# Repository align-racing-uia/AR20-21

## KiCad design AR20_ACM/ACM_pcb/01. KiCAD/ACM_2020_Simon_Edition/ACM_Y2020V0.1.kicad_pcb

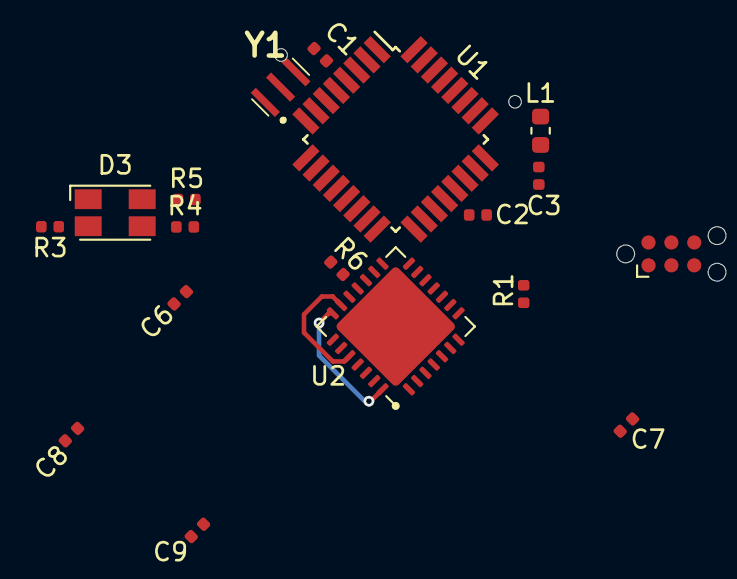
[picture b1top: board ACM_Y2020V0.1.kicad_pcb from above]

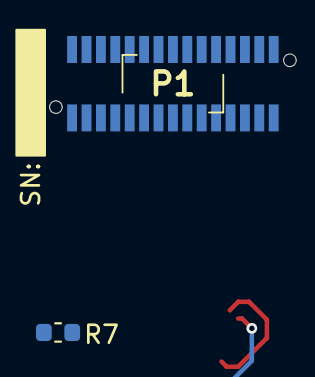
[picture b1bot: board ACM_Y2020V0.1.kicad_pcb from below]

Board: 2 copper layers, 21 parts (2 on the bottom side), 36 nets.

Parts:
C1, C2, C3, C6, C7, C8, C9: 0.1uF; C_0402_1005Metric
D3: ASMB-MTB0-0A3A2; LED_Avago_PLCC4_3.2x2.8mm_CW
H1: M2 Mouting hole; MountingHole_2.2mm_M2
J1: TC2030-MCP-NL; Tag-Connect_TC2030-IDC-NL_2x03_P1.27mm_Vertical
L1: 10uH; L_0603_1608Metric
P1: Conn_02x15_Odd_Even; ILWX10SBVFBE
R1, R6: 10K Ohm; R_0402_1005Metric
R3: 290 ohm; R_0402_1005Metric
R4: 200ohm; R_0402_1005Metric
R5: 190 Ohm; R_0402_1005Metric
R7: 120 Ohm; R_0603_1608Metric
U1: ATmega328P-AU; TQFP-32_7x7mm_P0.8mm
U2: MCP25625-x-SS; QFN-28-1EP_6x6mm_P0.65mm_EP4.8x4.8mm
Y1: 16.0Mhz; CSTNE16M0V530000R0

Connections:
+5V: C1.1, C6.1, D3.1, J1.2, L1.1, P1.27, R1.1, R6.2, U1.4, U1.6, U1.18
/BLUE_LED: P1.19, R5.2, U1.14
/CAN_CS: U1.11, U2.17
/CAN_INT: U1.32, U2.13
/CLK_MCP: U1.12, U2.9
/GREEN_LED: P1.25, R4.2, U1.9
/MISO: J1.1, P1.15, U1.16, U2.16
/MOSI: J1.4, P1.17, U1.15, U2.15
/RED_LED: P1.21, R3.2, U1.13
/Reset: J1.5, P1.10, R1.2
/SCK: J1.3, P1.13, U1.17, U2.14
/U-Pin1: P1.1, R7.2, U2.3
/U-Pin2: P1.2, U1.25
/U-Pin3: P1.3, R7.1, U2.4
/U-Pin4: P1.4, U1.26
/U-Pin6: P1.6, U1.27
/U-Pin7: P1.7, U1.23
/U-Pin8: P1.8, U1.28
/U-Pin12: P1.12, U1.30
/U-Pin14: P1.14, U1.31
/U-Pin20: P1.20, U1.1
/U-Pin22: P1.22, U1.2
/U-Pin23: P1.23, U1.10
GND: C1.2, C2.2, C3.1, C6.2, C7.2, C8.2, C9.1, J1.6, P1.16, P1.18, U1.3, U1.5, U1.21, U2.5, U2.10, U2.26, Y1.2
unnamed: C2.1, U1.20
unnamed: C3.2, L1.2
unnamed: C7.1, C8.1, U2.1, U2.19
unnamed: C9.2, U2.27
unnamed: D3.2, R5.1
unnamed: D3.3, R4.1
unnamed: D3.4, R3.1
unnamed: R6.1, U2.18
unnamed: U1.7, Y1.3
unnamed: U1.8, Y1.1
unnamed: U2.20, U2.24
unnamed: U2.21, U2.28

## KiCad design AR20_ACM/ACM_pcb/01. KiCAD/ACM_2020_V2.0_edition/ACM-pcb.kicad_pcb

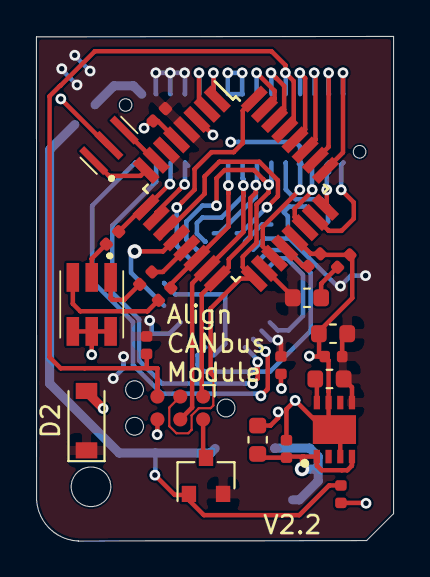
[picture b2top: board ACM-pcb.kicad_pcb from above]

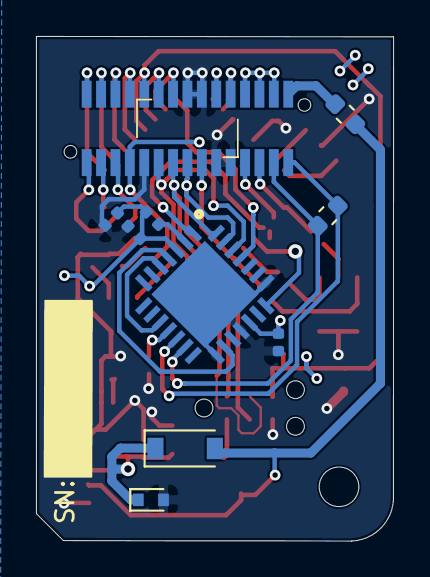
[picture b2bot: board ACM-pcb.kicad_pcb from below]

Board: 2 copper layers, 19.8 x 28.0 mm, 33 parts (11 on the bottom side), 42 nets.

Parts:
C1, C2, C3, C4, C5, C6, C7, C8, C9: 0.1uF; C_0402_1005Metric
C10, C11: 10uF; C_0603_1608Metric
D1: 15V; D_SOD-523
D2: D_Zener_KDZVTR5.6B; D_Zener_KDZV5.6B_SOD-123
D4: D_Schottky_MBR0520LT1G; D_schotky_MBR0520LT1G
F1: 250mA; Fuse_0603_1608Metric
H1: M2 Mouting hole; MountingHole_2.2mm_M2
IC1: MCP25625T-E_ML; QFN65P600X600X100-29N-D
J1: TC2030-MCP-NL; Tag-Connect_TC2030-IDC-NL_2x03_P1.27mm_Vertical
L1: 10uH; L_0603_1608Metric
L2: 2.2 µH; L_0603_1608Metric
LED1: ASMB-TTF0-0A20B; ASMBTTF00A20B
P1: Conn_02x15_Odd_Even; ILWX10SBVFBE
Q1: Q_PMOS_DMP3099L-13; Pmos_DMP3099L-13
R1, R2, R6: 10K Ohm; R_0402_1005Metric
R3: 290 ohm; R_0402_1005Metric
R4: 200ohm; R_0402_1005Metric
R5: 190 Ohm; R_0402_1005Metric
R7: 120 Ohm; R_0603_1608Metric
U1: ATmega328P-AU; TQFP-32_7x7mm_P0.8mm
U3: NCV890430MW50TXG; SON65P300X300X100-9N
Y1: 16.0Mhz; CSTNE16M0V530000R0

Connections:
12V_fused: D4.2, F1.1, Q1.1, R2.2
+5V: C1.1, C5.1, C6.1, C7.1, C8.1, C9.2, C11.1, D2.1, IC1.3, IC1.11, IC1.19, L1.1, L2.2, P1.24, P1.26, P1.28, Q1.2, R1.1, R6.2, U1.4, U1.6, U1.18, U3.5
+12V: F1.2, P1.30
+12V_Safe: C4.1, C10.1, D1.1, D4.1, U3.1, U3.4
/BLUE_LED: P1.17, R5.2, U1.14
/CAN_CS: IC1.1, U1.11
/CAN_INT: IC1.25, U1.32
/CLK_MCP: IC1.21, U1.12
/GREEN_LED: P1.25, R4.2, U1.9
/MISO: IC1.28, J1.1, P1.13, U1.16
/MOSI: IC1.27, J1.4, P1.15, U1.15
/RED_LED: R3.2, U1.13
/Reset: J1.5, P1.10, R1.2, U1.29
/SCK: IC1.26, J1.3, P1.11, U1.17
/U-Pin1: P1.1, U1.23
/U-Pin2: P1.2, U1.25
/U-Pin3: P1.3, U1.24
/U-Pin4: P1.4, U1.26
/U-Pin5: P1.5, U1.22
/U-Pin6: P1.6, U1.27
/U-Pin7: P1.7, U1.19
/U-Pin8: P1.8, U1.28
/U-Pin12: P1.12, U1.30
/U-Pin14: P1.14, U1.31
/U-Pin20: P1.20, U1.1
/U-Pin22: P1.22, U1.2
/U-Pin23: P1.23, U1.10
/U-Pin27: IC1.13, P1.27, R7.1
/U-Pin29: IC1.12, P1.29, R7.2
GND: C1.2, C2.2, C3.1, C4.2, C5.2, C6.2, C7.2, C8.2, C9.1, C10.2, C11.2, D1.2, D2.2, IC1.15, IC1.18, IC1.22, IC1.29, J1.6, LED1.2, LED1.4, LED1.6, P1.9, P1.16, P1.18, P1.19, P1.21, R2.1, U1.3, U1.5, U1.21, U3.3, U3.7, U3.9, Y1.2
unnamed: C2.1, U1.20
unnamed: C3.2, L1.2
unnamed: IC1.2, R6.1
unnamed: IC1.5, IC1.10
unnamed: IC1.4, IC1.16
unnamed: J1.2, Q1.3
unnamed: L2.1, U3.8
unnamed: LED1.1, R3.1
unnamed: LED1.3, R4.1
unnamed: LED1.5, R5.1
unnamed: U1.7, Y1.3
unnamed: U1.8, Y1.1

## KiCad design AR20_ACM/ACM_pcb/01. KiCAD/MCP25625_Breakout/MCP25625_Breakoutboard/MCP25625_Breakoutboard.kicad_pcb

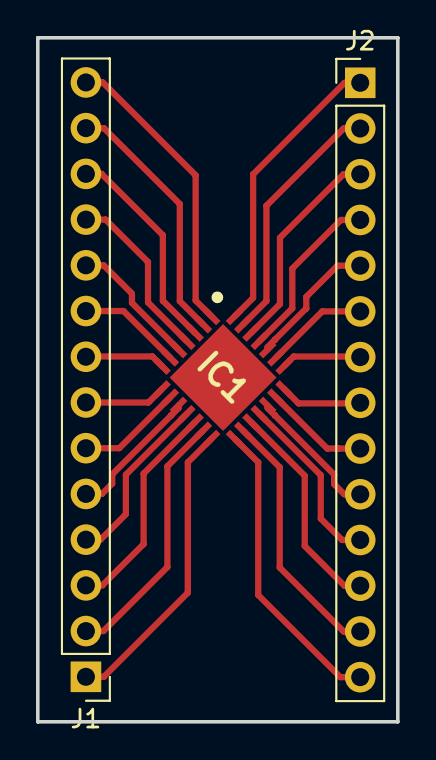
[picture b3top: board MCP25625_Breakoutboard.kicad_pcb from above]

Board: 2 copper layers, 20.0 x 38.0 mm, 3 parts (0 on the bottom side), 28 nets.

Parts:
IC1: MCP25625T-E_ML; QFN65P600X600X100-29N-D
J1, J2: Conn_01x14; PinHeader_1x14_P2.54mm_Vertical

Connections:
/Pin1: IC1.1, J1.14
/Pin2: IC1.2, J1.13
/Pin3: IC1.3, J1.12
/Pin4: IC1.4, J1.11
/Pin5: IC1.5, J1.10
/Pin6: IC1.6, J1.9
/Pin7: IC1.7, J1.8
/Pin8: IC1.8, J1.7
/Pin9: IC1.9, J1.6
/Pin10: IC1.10, J1.5
/Pin11: IC1.11, J1.4
/Pin12: IC1.12, J1.3
/Pin13: IC1.13, J1.2
/Pin14: IC1.14, J1.1
/Pin15: IC1.15, J2.14
/Pin16: IC1.16, J2.13
/Pin17: IC1.17, J2.12
/Pin18: IC1.18, J2.11
/Pin19: IC1.19, J2.10
/Pin20: IC1.20, J2.9
/Pin21: IC1.21, J2.8
/Pin22: IC1.22, J2.7
/Pin23: IC1.23, J2.6
/Pin24: IC1.24, J2.5
/Pin25: IC1.25, J2.4
/Pin26: IC1.26, J2.3
/Pin27: IC1.27, J2.2
/Pin28: IC1.28, J2.1

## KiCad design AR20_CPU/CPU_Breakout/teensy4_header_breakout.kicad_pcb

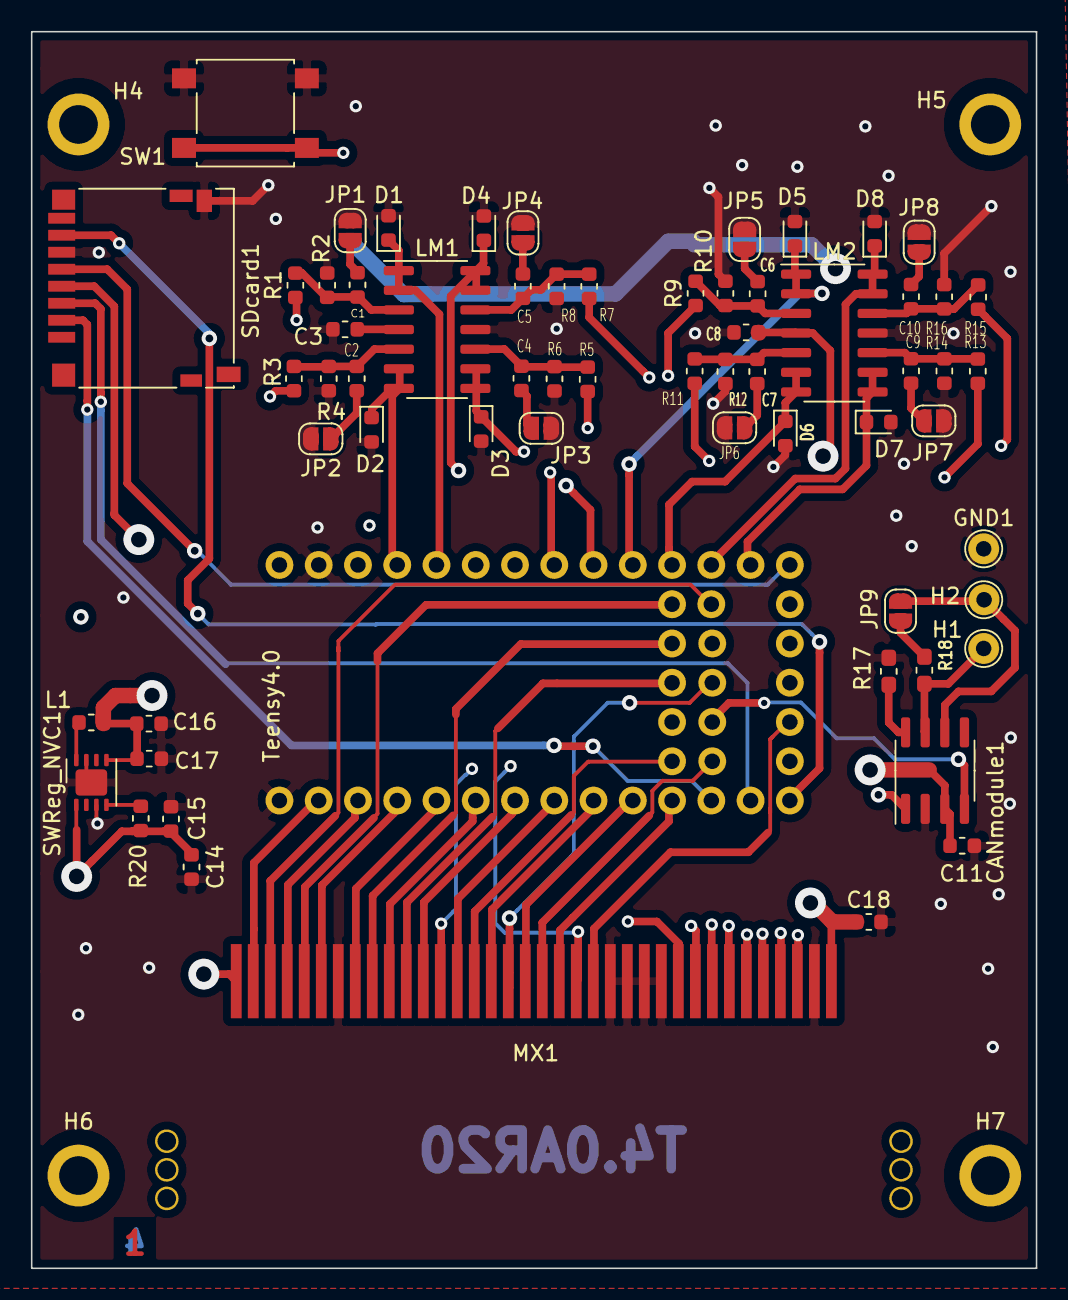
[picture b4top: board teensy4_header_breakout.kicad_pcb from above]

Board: 4 copper layers, 65.0 x 80.0 mm, 69 parts (0 on the bottom side), 69 nets.

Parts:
BT1: 3V cell coin; BatteryHolder_Keystone_3034_1x20mm
C1, C2, C4, C5, C6, C7, C9, C10: 1.5n; C_0603_1608Metric
C3, C8: C; C_0603_1608Metric
C11: .1u; C_0603_1608Metric
C14, C17, C18: 10u; C_0603_1608Metric
C15, C16: 0.1u; C_0603_1608Metric
CANmodule1: MCP2551-I-SN; SOIC-8_3.9x4.9mm_P1.27mm
D1, D2, D3, D4, D5, D6, D7, D8: 3V; D_0603_1608Metric
GND1: GND; TestPoint_THTPad_D2.0mm_Drill1.0mm
H1: CANH_out; TestPoint_THTPad_D2.0mm_Drill1.0mm
H2: CANL_out; TestPoint_THTPad_D2.0mm_Drill1.0mm
H4, H5, H6, H7: MountingHole; MountingHole_2.5mm_Pad
JP1, JP2, JP3, JP4, JP5, JP6, JP7, JP8: SJ_Open; SolderJumper-2_P1.3mm_Open_RoundedPad1.0x1.5mm
JP9: SolderJumper_2_Open; SolderJumper-2_P1.3mm_Open_RoundedPad1.0x1.5mm
L1: 2.2u; L_0603_1608Metric
LM1, LM2: LM324DRG3; SOIC-14_3.9x8.7mm_P1.27mm
MX1: MX34_36_pins; Connector_MX34_36pins
R1, R3, R5, R7, R9, R11, R13, R15, R20: 10k; R_0603_1608Metric
R2, R4, R6, R8, R10, R12, R14, R16: 20k; R_0603_1608Metric
R17: 60; R_0603_1608Metric_Pad1.05x0.95mm_HandSolder
R18: 120; R_0603_1608Metric_Pad1.05x0.95mm_HandSolder
SDcard1: Micro_SD_Card; microSD_HC_Hirose_DM3D-SF
SW1: SW_Push_Dual; SW_SPST_B3S-1000
SWReg_NVC1: NCV890430MW50TXG; DFN-8-1EP_3x3mm_P0.65mm_EP1.7x2.05mm
Teensy4.0: Teensy_pins; Teensy_40_footprint

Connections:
0_RX1: MX1.1, Teensy4.0.3
1_TX1: MX1.3, Teensy4.0.5
2_OUT2: MX1.5, Teensy4.0.7
3.3V: MX1.21, SDcard1.4, Teensy4.0.6, Teensy4.0.30
3_LRCLK2: MX1.7, Teensy4.0.9
4_BCLK2: MX1.9, Teensy4.0.11
5_IN2: MX1.11, Teensy4.0.13
6_OUT1D: MX1.13, Teensy4.0.15
7_RX2_OUT1A: MX1.15, Teensy4.0.17
8_TX2_IN1: MX1.17, Teensy4.0.19
9_OUT1C: MX1.19, Teensy4.0.21
10_CS: SDcard1.2, Teensy4.0.23
11_MOSI: SDcard1.3, Teensy4.0.25
12V_IN: C14.1, C15.1, C18.1, MX1.52, R20.1, SWReg_NVC1.1
12_MISO: SDcard1.7, Teensy4.0.27
13(LED): SDcard1.5, Teensy4.0.28
20_TX5: MX1.39, Teensy4.0.14
21_RX5: MX1.37, Teensy4.0.12
24_TX6_A10: MX1.22, Teensy4.0.38
25_RX6_A11: MX1.24, Teensy4.0.43
27_A13: MX1.38, Teensy4.0.42
28_RX7: MX1.36, Teensy4.0.36
29_TX7: MX1.42, Teensy4.0.41
30_CRX3: CANmodule1.4, Teensy4.0.35
31_CTX3: CANmodule1.1, Teensy4.0.40
32_OUT1B: MX1.40, Teensy4.0.34
33_MCLK2: MX1.41, Teensy4.0.39
Ground: BT1.2, C3.1, C8.1, C11.2, C14.2, C15.2, C16.2, C17.2, C18.2, CANmodule1.2, D1.2, D2.2, D3.2, D4.2, D5.2, D6.2, D7.2, D8.2, GND1.1, JP1.2, JP2.2, JP3.2, JP4.2, JP5.2, JP6.2, JP7.2, JP8.2, LM1.11, LM2.11, MX1.26, MX1.30, MX1.34, MX1.35, MX1.43, MX1.GND, R2.2, R4.2, R6.2, R8.2, R10.2, R12.2, R14.2, R16.2, R17.1, SDcard1.6, SDcard1.9, SW1.1, SWReg_NVC1.3, SWReg_NVC1.7, SWReg_NVC1.9, Teensy4.0.1, Teensy4.0.4, Teensy4.0.31
IN1+: C1.1, LM1.3, R1.2, R2.1
IN2+: C2.1, LM1.5, R3.2, R4.1
IN3+: C4.1, LM1.10, R5.2, R6.1
IN4+: C5.1, LM1.12, R7.2, R8.1
IN5+: C6.1, LM2.3, R9.2, R10.1
IN6+: C7.1, LM2.5, R11.2, R12.1
IN7+: C9.1, LM2.10, R13.2, R14.1
IN8+: C10.1, LM2.12, R15.2, R16.1
unnamed: C1.2, JP1.1
unnamed: C2.2, JP2.1
unnamed: C4.2, JP3.1
unnamed: C5.2, JP4.1
unnamed: C6.2, JP5.1
unnamed: C7.2, JP6.1
unnamed: C9.2, JP7.1
unnamed: C10.2, JP8.1
unnamed: CANmodule1.6, H2.1, JP9.2
unnamed: CANmodule1.7, H1.1, R18.1
unnamed: CANmodule1.8, R17.2
unnamed: JP9.1, R18.2
unnamed: L1.1, SWReg_NVC1.8
unnamed: R20.2, SWReg_NVC1.4
ON_OFF: SW1.2, Teensy4.0.33
Out1: D1.1, LM1.1, LM1.2, Teensy4.0.10
Out2: D2.1, LM1.6, LM1.7, Teensy4.0.8
Out3: D3.1, LM1.8, LM1.9, Teensy4.0.16
Out4: D4.1, LM1.13, LM1.14, Teensy4.0.18
Out5: D5.1, LM2.1, LM2.2, Teensy4.0.20
Out6: D6.1, LM2.6, LM2.7, Teensy4.0.22
Out7: D7.1, LM2.8, LM2.9, Teensy4.0.26
Out8: D8.1, LM2.13, LM2.14, Teensy4.0.24
Sensor_Input_1: MX1.44, R1.1
Sensor_Input_2: MX1.45, R3.1
Sensor_Input_3: MX1.46, R5.1
Sensor_Input_4: MX1.47, R7.1
Sensor_Input_5: MX1.48, R9.1
Sensor_Input_6: MX1.49, R11.1
Sensor_Input_7: MX1.50, R13.1
Sensor_Input_8: MX1.51, R15.1
VBAT: BT1.1, Teensy4.0.29
Vinn_5V: C3.2, C8.2, C11.1, C16.1, C17.1, CANmodule1.3, L1.2, LM1.4, LM2.4, MX1.20, SWReg_NVC1.5, Teensy4.0.2
